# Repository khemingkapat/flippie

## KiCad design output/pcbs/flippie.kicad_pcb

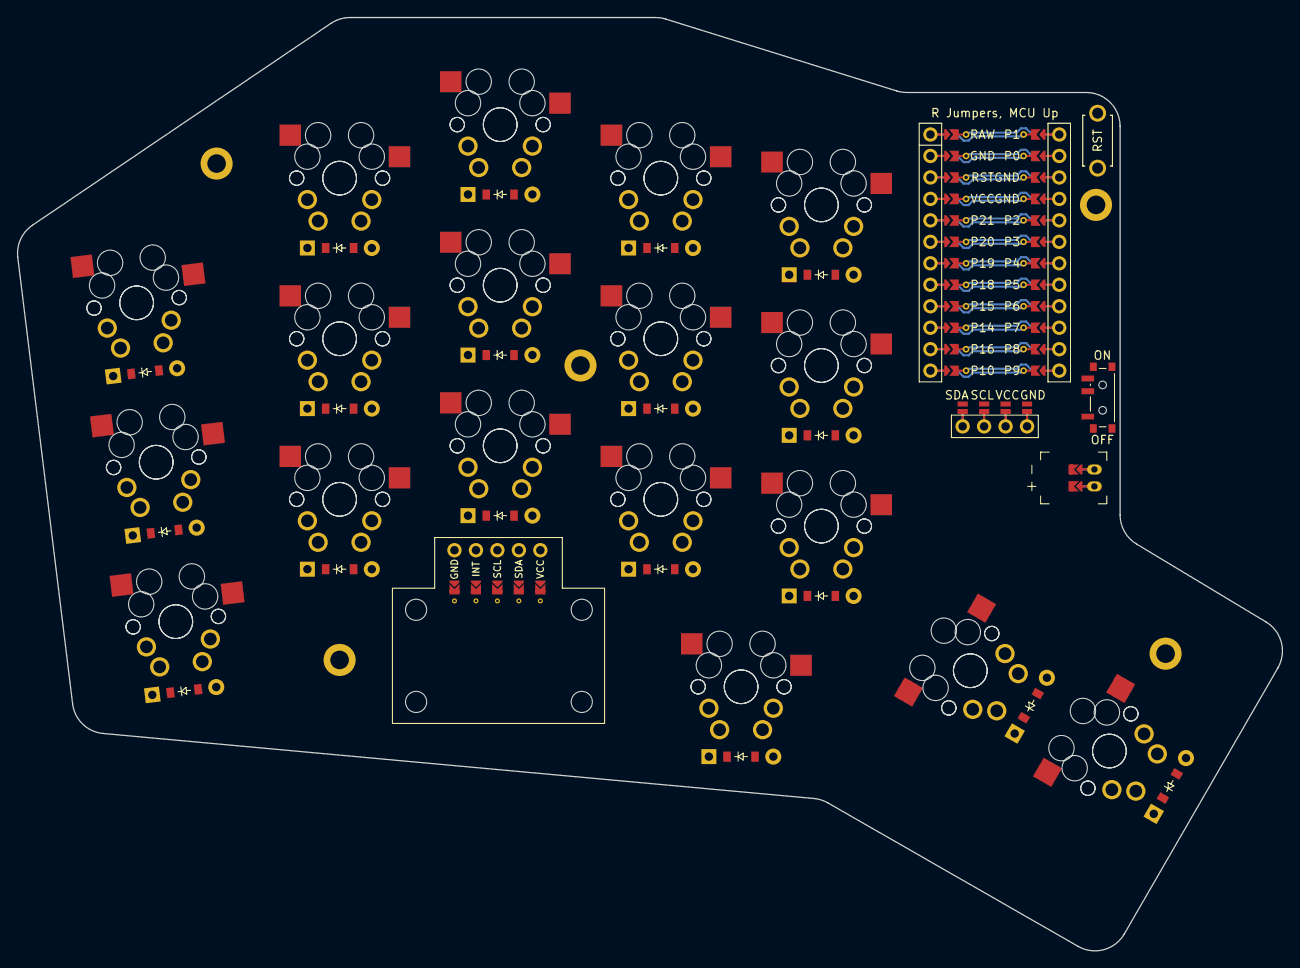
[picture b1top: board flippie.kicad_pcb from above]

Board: 2 copper layers, 149.6 x 110.4 mm, 64 parts (0 on the bottom side), 40 nets.

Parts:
D1, D2, D3, D4, D5, D6, D7, D8, D9, D10, D11, D12, D13, D14, D15, D16, D17, D18: ComboDiode
DISP1: display_ssd1306
H1, H2, H3, H4, H5: mounting_hole_plated
JST1: battery_connector_jst_ph_2
MCU1: mcu_nice_nano
PWR1: power_switch_smd_side
RST1: reset_switch_tht_top
S1, S2, S3, S4, S5, S6, S7, S8, S9, S10, S11, S12, S13, S14, S15, S16, S17, S18, S19, S20, S21, S22, S23, S24, S25, S26, S27, S28, S29, S30, S31, S32, S33, S34, S35, S36: MX

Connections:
BAT_P: JST1.1, PWR1.1, PWR1.3
DISP1_1: DISP1.1, DISP1.10, DISP1.23
DISP1_2: DISP1.2, DISP1.11, DISP1.22
DISP1_3: DISP1.3, DISP1.12, DISP1.21
DISP1_4: DISP1.4, DISP1.13, DISP1.20
GND: DISP1.14, DISP1.24, JST1.2, MCU1.103, MCU1.104, MCU1.123, RST1.2
JST1_1: JST1.11, JST1.21, JST1.31
JST1_2: JST1.12, JST1.22, JST1.32
P2: DISP1.17, DISP1.27, MCU1.105
P3: DISP1.16, DISP1.26, MCU1.106
P9: D16.1, D17.1, D18.1, MCU1.112
P10: D1.1, D4.1, D7.1, D10.1, D13.1, MCU1.113
P14: D3.1, D6.1, D9.1, D12.1, D15.1, MCU1.115
P15: MCU1.116, S13.1, S14.1, S15.1, S18.1, S31.1, S32.1, S33.1, S36.1
P16: D2.1, D5.1, D8.1, D11.1, D14.1, MCU1.114
P18: MCU1.117, S10.1, S11.1, S12.1, S17.1, S28.1, S29.1, S30.1, S35.1
P19: MCU1.118, S7.1, S8.1, S9.1, S16.1, S25.1, S26.1, S27.1, S34.1
P20: MCU1.119, S4.1, S5.1, S6.1, S22.1, S23.1, S24.1
P21: MCU1.120, S1.1, S2.1, S3.1, S19.1, S20.1, S21.1
RAW: MCU1.124, PWR1.2
RST: MCU1.122, RST1.1
VCC: DISP1.15, DISP1.25, MCU1.121
index_bottom: D10.2, S10.2, S28.2
index_home: D11.2, S11.2, S29.2
index_top: D12.2, S12.2, S30.2
inner_cluster: D16.2, S16.2, S34.2
middle_bottom: D7.2, S7.2, S25.2
middle_cluster: D17.2, S17.2, S35.2
middle_home: D8.2, S8.2, S26.2
middle_top: D9.2, S9.2, S27.2
pinky_bottom: D1.2, S1.2, S19.2
pinky_home: D2.2, S2.2, S20.2
pinky_top: D3.2, S3.2, S21.2
reach_bottom: D13.2, S13.2, S31.2
reach_cluster: D18.2, S18.2, S36.2
reach_home: D14.2, S14.2, S32.2
reach_top: D15.2, S15.2, S33.2
ring_bottom: D4.2, S4.2, S22.2
ring_home: D5.2, S5.2, S23.2
ring_top: D6.2, S6.2, S24.2

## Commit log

2024-06-06 config file from ergogen web
2024-06-06 additional footprint
2024-06-06 output file
2024-06-06 config nets
2024-06-06 move file here and config some params
2024-06-06 remove unused file
2024-06-06 reconfig the size of pcb
2024-06-06 adding diodes and testing on jst
2024-06-07 added external footprints
2024-06-07 added footprint
2024-06-07 remove unused line
2024-06-07 resize
2024-06-08 adding optional key
2024-06-08 remove optional
    remove optional key due to insufficient size
2024-06-08 working with custom reversible pimoroni
2024-06-09 adding local net for reversible footprint
2024-06-09 rename to flippie
2024-06-09 move mcu
2024-06-11 adding oled
2024-06-21 creating through holes for pimonori for easier routing
2024-06-22 make it take less space
2024-06-22 adding missing traces and mounting holes
2024-07-08 reconfig to create plate and backplate
2024-07-10 fix plate cutout
2024-07-16 add jst cutout instead of remove the whole part
2024-07-17 smaller jst cutout
2024-08-04 fix cutout
2024-08-05 moving cutout out of the way
